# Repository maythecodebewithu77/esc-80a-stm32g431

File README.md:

Hardware design of a drone motor controller (ESC) built around the
STM32G431CBU6 microcontroller and the DRV8302 gate driver. Designed in KiCad.

## Status
- Schematic: complete and reviewed
- PCB layout: [in progress / completed / handed to a layout designer]
- Firmware: not started
- Hardware testing: not done yet

## Main specifications
- Input voltage: up to 25 V
- Current: 80 A (design target)
- Microcontroller: STM32G431CBU6
- Gate driver: DRV8302
- Power supply: LMR16020 (25 V to 12 V), TPS54331 (12 V to 3.3 V)
- Power MOSFETs: NVMFS5C638NLT1G

## Design notes
- Planned 4-layer PCB: signal, ground, power, signal, with 2 oz copper
- Errors found and fixed during design review: PWM pin mapping,
  current-sense wiring, reverse-polarity MOSFET size, ADC clamp diode

## Folders
- `hardware/` KiCad project files
- `docs/` schematic and design notes

## Next steps
- Complete PCB layout and thermal checks
- Write and test firmware

## Author
Vigneshwar S, ECE student, SRM IST

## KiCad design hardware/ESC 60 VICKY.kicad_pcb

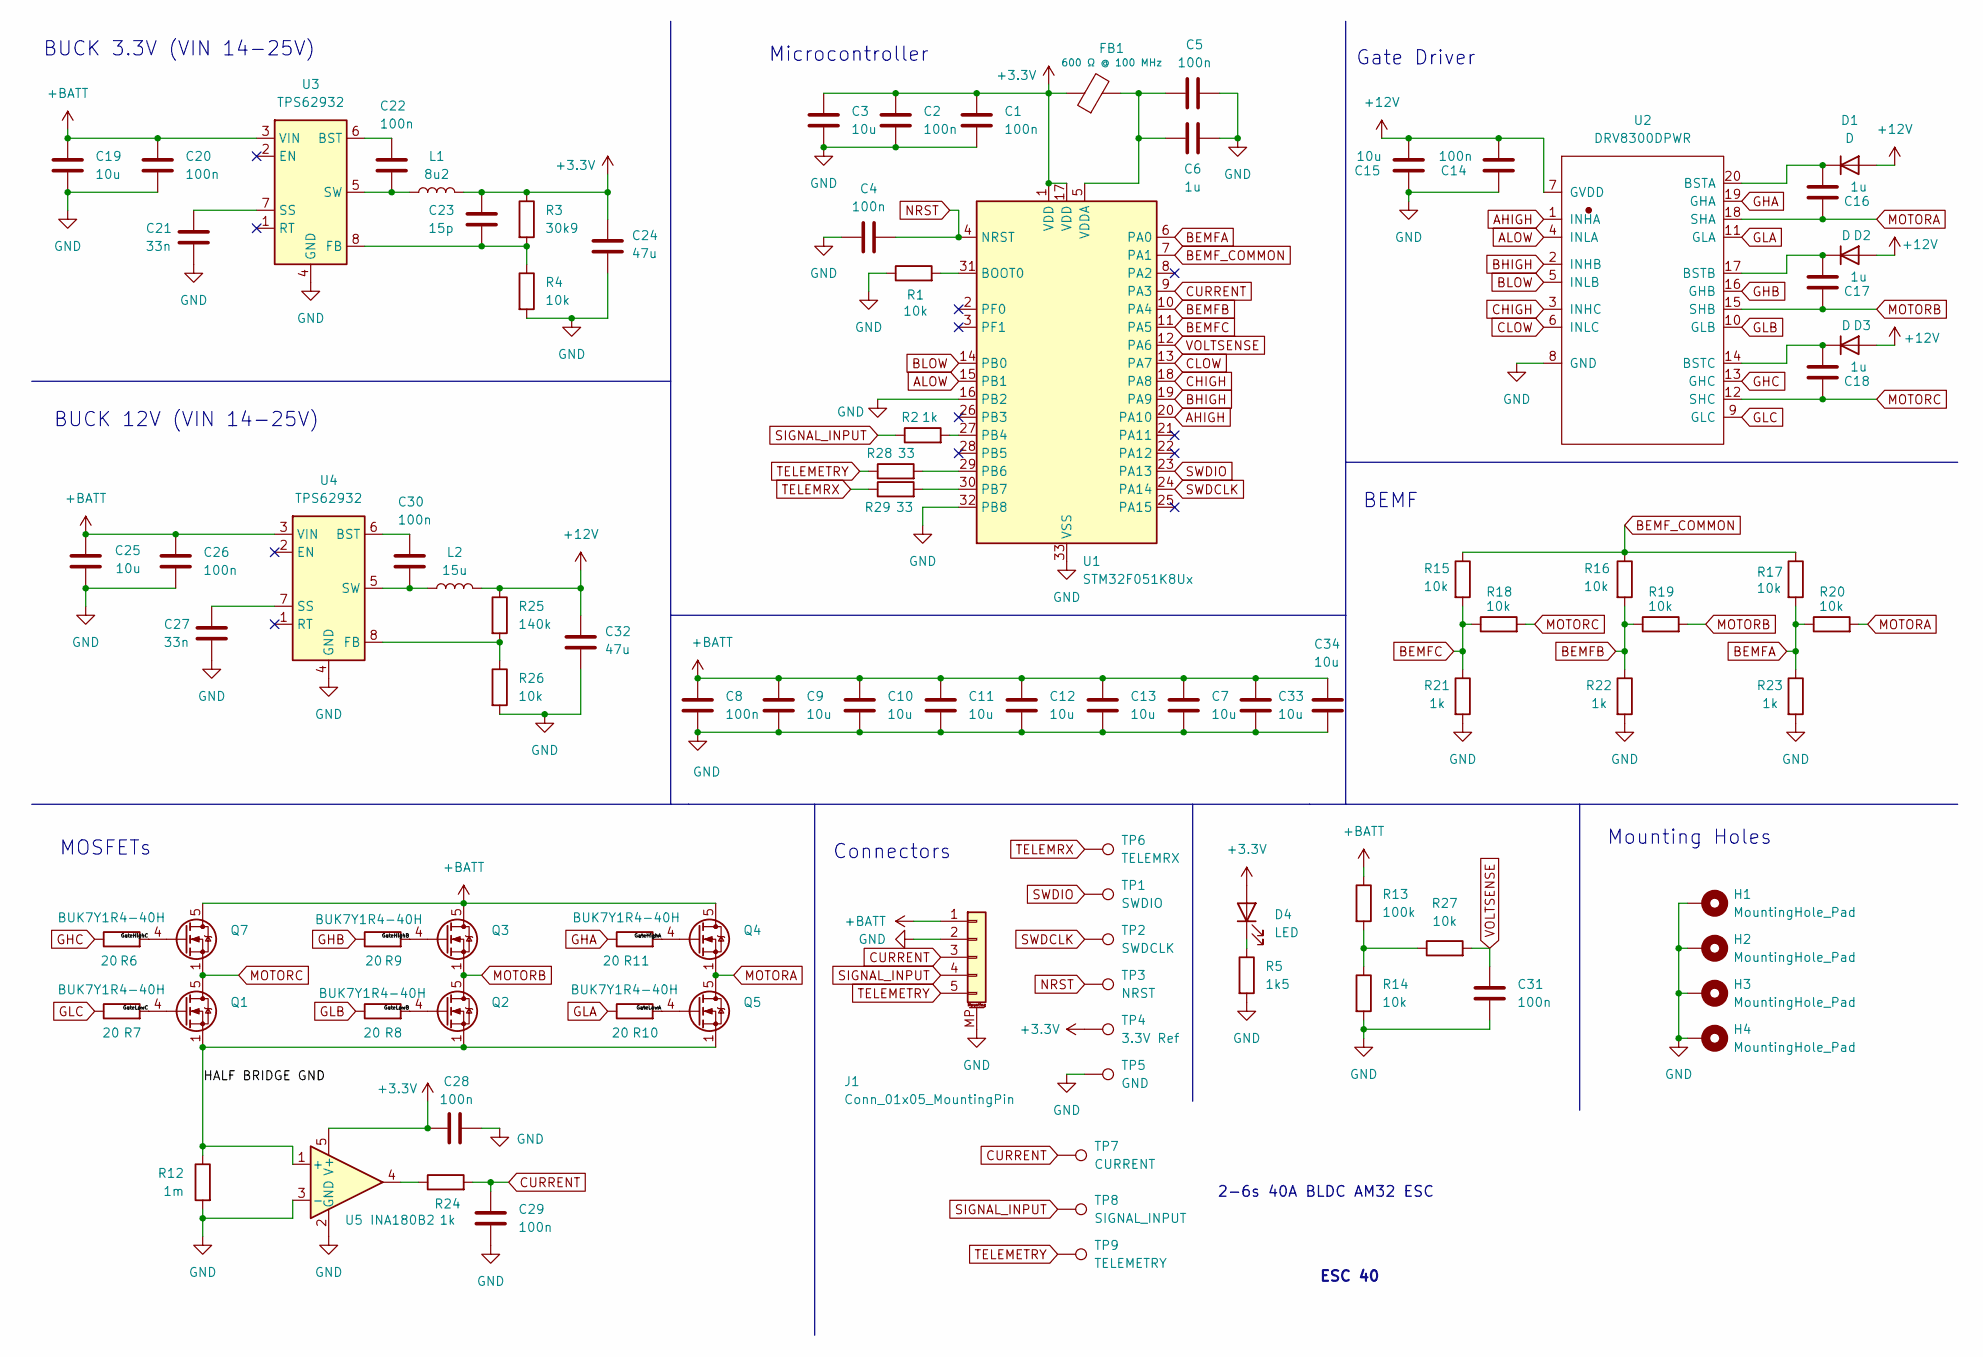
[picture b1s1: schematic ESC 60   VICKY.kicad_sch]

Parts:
C1, C2, C4, C5, C14, C22, C28, C29, C30, C31: 100n; C_0402_1005Metric; Manufacturer Part Number CA0522618; LCSC Part # C307331
C3, C15: 10u; C_0603_1608Metric; LCSC Part # C96446
C6: 1u; C_0402_1005Metric; LCSC Part # C52923
C7, C9, C10, C11, C12, C13, C33, C34: 10u; C_1210_3225Metric; LCSC Part # C53084452
C8: 100n; C_1210_3225Metric; LCSC Part # C2179722
C16, C17, C18: 1u; C_0603_1608Metric; LCSC Part # C15849
C19, C25: 10u; C_0805_2012Metric; LCSC Part # C440198
C20, C26: 100n; C_0603_1608Metric; LCSC Part # C14663
C21, C27: 33n; C_0402_1005Metric; LCSC Part # C106862
C23: 15p; C_0402_1005Metric; LCSC Part # C1548
C24, C32: 47u; C_1210_3225Metric; LCSC Part # C77101
D1, D2, D3: D; D_SMA; LCSC Part # C2480
D4: LED; LED_0603_1608Metric; LCSC Part # C111340
FB1: 600 Ω @ 100 MHz; L_0603_1608Metric; LCSC Part # C85833
H1, H2, H3, H4: MountingHole_Pad; MountingHole_4.3mm_M4_ISO14580_Pad
J1: Conn_01x05_MountingPin; JST_GH_SM05B-GHS-TB_1x05-1MP_P1.25mm_Horizontal; LCSC Part # C189896
L1: 8u2; L_KOHERelec_MDA7030; LCSC Part # C436550
L2: 15u; L_KOHERelec_MDA7030; LCSC Part # C2847486
Q1, Q2, Q3, Q4, Q5, Q7: BUK7Y1R4-40H; LFPAK56; LCSC Part # C6423721
R1, R4, R14, R15, R16, R17, R18, R19, R20, R26, R27: 10k; R_0402_1005Metric; LCSC Part # C25744
R2, R21, R22, R23, R24: 1k; R_0402_1005Metric; LCSC Part # C11702
R3: 30k9; R_0402_1005Metric; LCSC Part # C270615
R5: 1k5; R_0402_1005Metric; LCSC Part # C25867
R6, R7, R8, R9, R10, R11: 20; R_0402_1005Metric; LCSC Part # C25089
R12: 1m; R_2512_6332Metric; LCSC Part # C469381
R13: 100k; R_0402_1005Metric; LCSC Part # C25741
R25: 140k; R_0402_1005Metric; LCSC Part # C114151
R28, R29: 33; R_0402_1005Metric; LCSC Part # C25105
TP1: SWDIO; TestPoint_THTPad_1.5x1.5mm_Drill0.7mm
TP2: SWDCLK; TestPoint_THTPad_1.5x1.5mm_Drill0.7mm
TP3: NRST; TestPoint_THTPad_1.5x1.5mm_Drill0.7mm
TP4: 3.3V Ref; TestPoint_THTPad_1.5x1.5mm_Drill0.7mm
TP5: GND; TestPoint_THTPad_1.5x1.5mm_Drill0.7mm
TP6: TELEMRX; TestPoint_THTPad_1.5x1.5mm_Drill0.7mm
TP7: CURRENT; TestPoint_THTPad_1.5x1.5mm_Drill0.7mm
TP8: SIGNAL_INPUT; TestPoint_THTPad_1.5x1.5mm_Drill0.7mm
TP9: TELEMETRY; TestPoint_THTPad_1.5x1.5mm_Drill0.7mm
U1: STM32F051K8Ux; QFN-32-1EP_5x5mm_P0.5mm_EP3.45x3.45mm; LCSC Part # C72339
U2: DRV8300DPWR; SOP65P640X120-20N; LCSC Part # C3036056
U3, U4: TPS62932; SOT-583-8; LCSC Part # C3032935
U5: INA180B2; SOT-23-5; LCSC Part # C2861539

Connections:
+3.3V: C1.1, C2.1, C3.1, C23.1, C24.1, C28.1, D4.2 (A), FB1.1, L1.2, R3.1, TP4.1, U1.1 (VDD), U1.17 (VDD), U5.5 (V+)
+12V: C14.2, C15.2, C32.1, D1.2 (A), D2.2 (A), D3.2 (A), L2.2, R25.1, U2.7 (GVDD)
+BATT: C7.1, C8.1, C9.1, C10.1, C11.1, C12.1, C13.1, C19.1, C20.1, C25.1, C26.1, C33.1, C34.1, J1.1, Q3.5 (D), Q4.5 (D), Q7.5 (D), R13.1, U3.3 (VIN), U4.3 (VIN)
/GateHighA: Q4.4 (G), R11.2
/GateHighB: Q3.4 (G), R9.2
/GateHighC: Q7.4 (G), R6.2
/GateLowA: Q5.4 (G), R10.2
/GateLowB: Q2.4 (G), R8.2
/GateLowC: Q1.4 (G), R7.2
/HALF BRIDGE GND: Q1.1 (S), Q1.2 (S), Q1.3 (S), Q2.1 (S), Q2.2 (S), Q2.3 (S), Q5.1 (S), Q5.2 (S), Q5.3 (S), R12.1, U5.1 (+)
AHIGH: U1.20 (PA10), U2.1 (INHA)
ALOW: U1.15 (PB1), U2.4 (INLA)
BEMFA: R17.2, R20.1, R23.1, U1.6 (PA0)
BEMFB: R16.2, R19.1, R22.1, U1.10 (PA4)
BEMFC: R15.2, R18.1, R21.1, U1.11 (PA5)
BEMF_COMMON: R15.1, R16.1, R17.1, U1.7 (PA1)
BHIGH: U1.19 (PA9), U2.2 (INHB)
BLOW: U1.14 (PB0), U2.5 (INLB)
CHIGH: U1.18 (PA8), U2.3 (INHC)
CLOW: U1.13 (PA7), U2.6 (INLC)
CURRENT: C29.1, J1.3, R24.2, TP7.1, U1.9 (PA3)
GHA: R11.1, U2.19 (GHA)
GHB: R9.1, U2.16 (GHB)
GHC: R6.1, U2.13 (GHC)
GLA: R10.1, U2.11 (GLA)
GLB: R8.1, U2.10 (GLB)
GLC: R7.1, U2.9 (GLC)
GND: C1.2, C2.2, C3.2, C4.1, C5.2, C6.2, C7.2, C8.2, C9.2, C10.2, C11.2, C12.2, C13.2, C14.1, C15.1, C19.2, C20.2, C21.2, C24.2, C25.2, C26.2, C27.2, C28.2, C29.2, C31.2, C32.2, C33.2, C34.2, H1.1, H2.1, H3.1, H4.1, J1.2, J1.MP (MountPin), R1.1, R4.2, R5.2, R12.2, R14.2, R21.2, R22.2, R23.2, R26.2, TP5.1, U1.16 (PB2), U1.32 (PB8), U1.33 (VSS), U2.8 (GND), U3.4 (GND), U4.4 (GND), U5.2 (GND), U5.3 (-)
MOTORA: C16.1, Q4.1 (S), Q4.2 (S), Q4.3 (S), Q5.5 (D), R20.2, U2.18 (SHA)
MOTORB: C17.1, Q2.5 (D), Q3.1 (S), Q3.2 (S), Q3.3 (S), R19.2, U2.15 (SHB)
MOTORC: C18.1, Q1.5 (D), Q7.1 (S), Q7.2 (S), Q7.3 (S), R18.2, U2.12 (SHC)
NRST: C4.2, TP3.1, U1.4 (NRST)
unnamed: C16.2, D1.1 (K), U2.20 (BSTA)
unnamed: C17.2, D2.1 (K), U2.17 (BSTB)
unnamed: C18.2, D3.1 (K), U2.14 (BSTC)
unnamed: D4.1 (K), R5.1
unnamed: R13.2, R14.1, R27.1
unnamed: R24.1, U5.4
unnamed: R1.2, U1.31 (BOOT0)
unnamed: R2.2, U1.27 (PB4)
unnamed: R28.2, U1.29 (PB6)
unnamed: R29.2, U1.30 (PB7)
unnamed: C5.1, C6.1, FB1.2, U1.5 (VDDA)
unnamed: C22.1, U3.6 (BST)
unnamed: C23.2, R3.2, R4.1, U3.8 (FB)
unnamed: C21.1, U3.7 (SS)
unnamed: C22.2, L1.1, U3.5 (SW)
unnamed: C30.1, U4.6 (BST)
unnamed: R25.2, R26.1, U4.8 (FB)
unnamed: C27.1, U4.7 (SS)
unnamed: C30.2, L2.1, U4.5 (SW)
SIGNAL_INPUT: J1.4, R2.1, TP8.1
SWDCLK: TP2.1, U1.24 (PA14)
SWDIO: TP1.1, U1.23 (PA13)
TELEMETRY: J1.5, R28.1, TP9.1
TELEMRX: R29.1, TP6.1
VOLTSENSE: C31.1, R27.2, U1.12 (PA6)

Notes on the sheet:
Microcontroller
ESC 40
BUCK 3.3V (VIN 14-25V)
Mounting Holes
BEMF
BUCK 12V (VIN 14-25V)
Connectors
MOSFETs
2-6s 40A BLDC AM32 ESC
Gate Driver

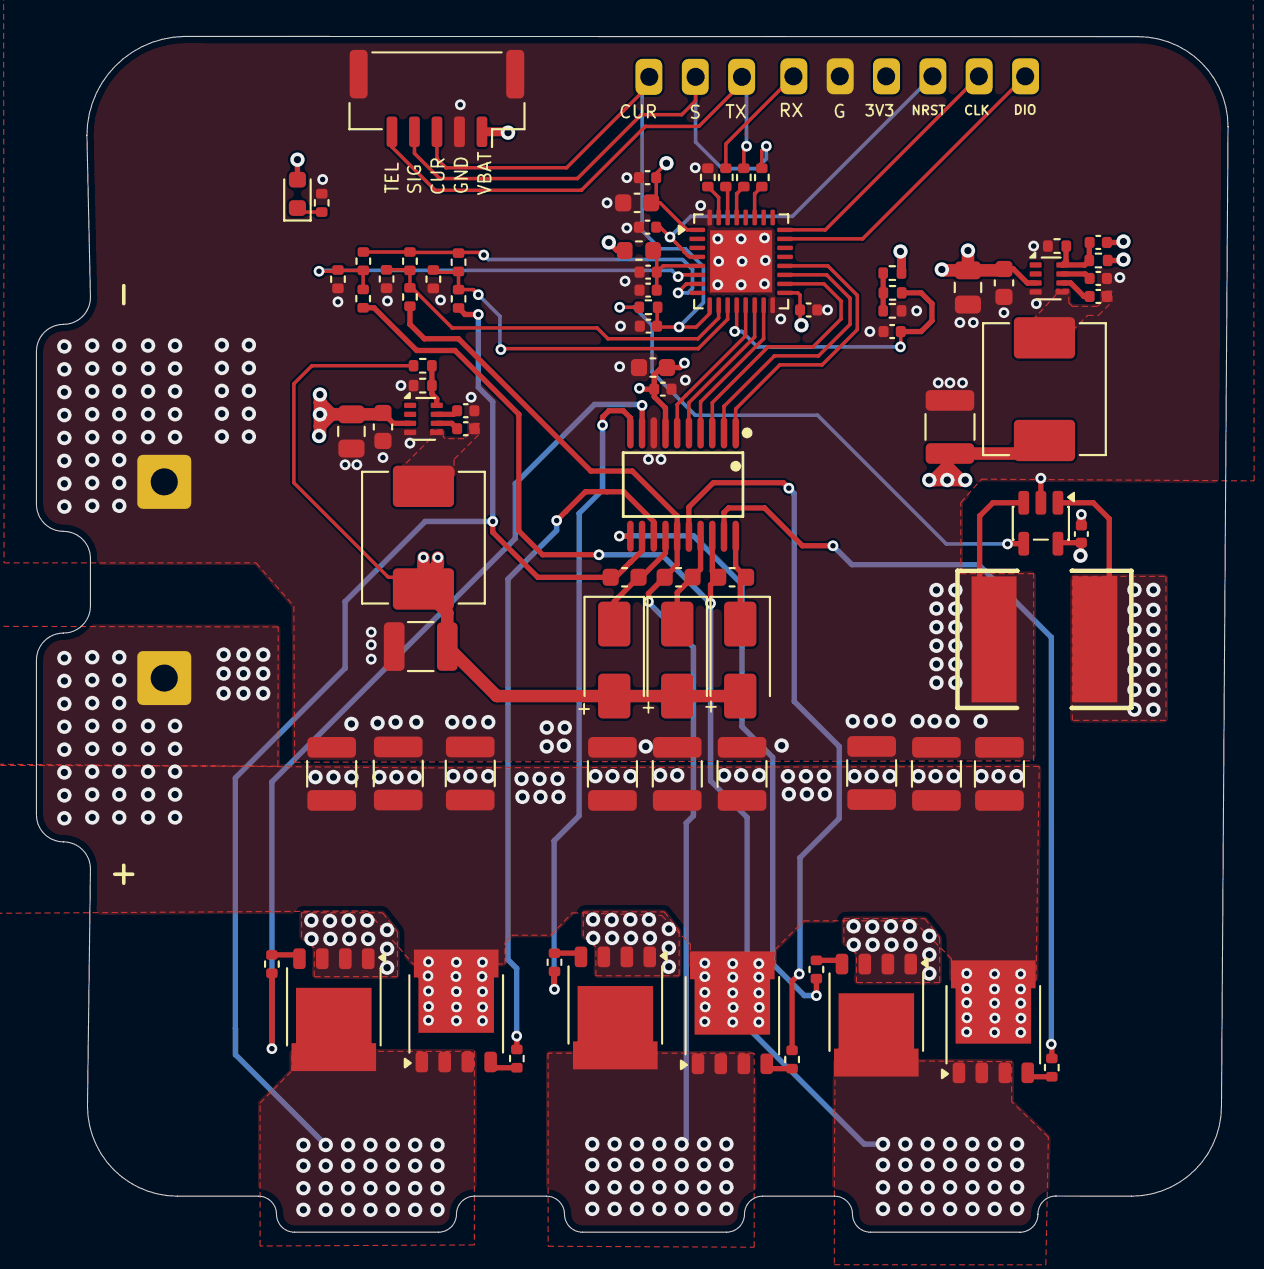
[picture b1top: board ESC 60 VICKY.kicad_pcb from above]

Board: 4 copper layers, 66.2 x 66.4 mm, 91 parts (0 on the bottom side), 57 nets.
